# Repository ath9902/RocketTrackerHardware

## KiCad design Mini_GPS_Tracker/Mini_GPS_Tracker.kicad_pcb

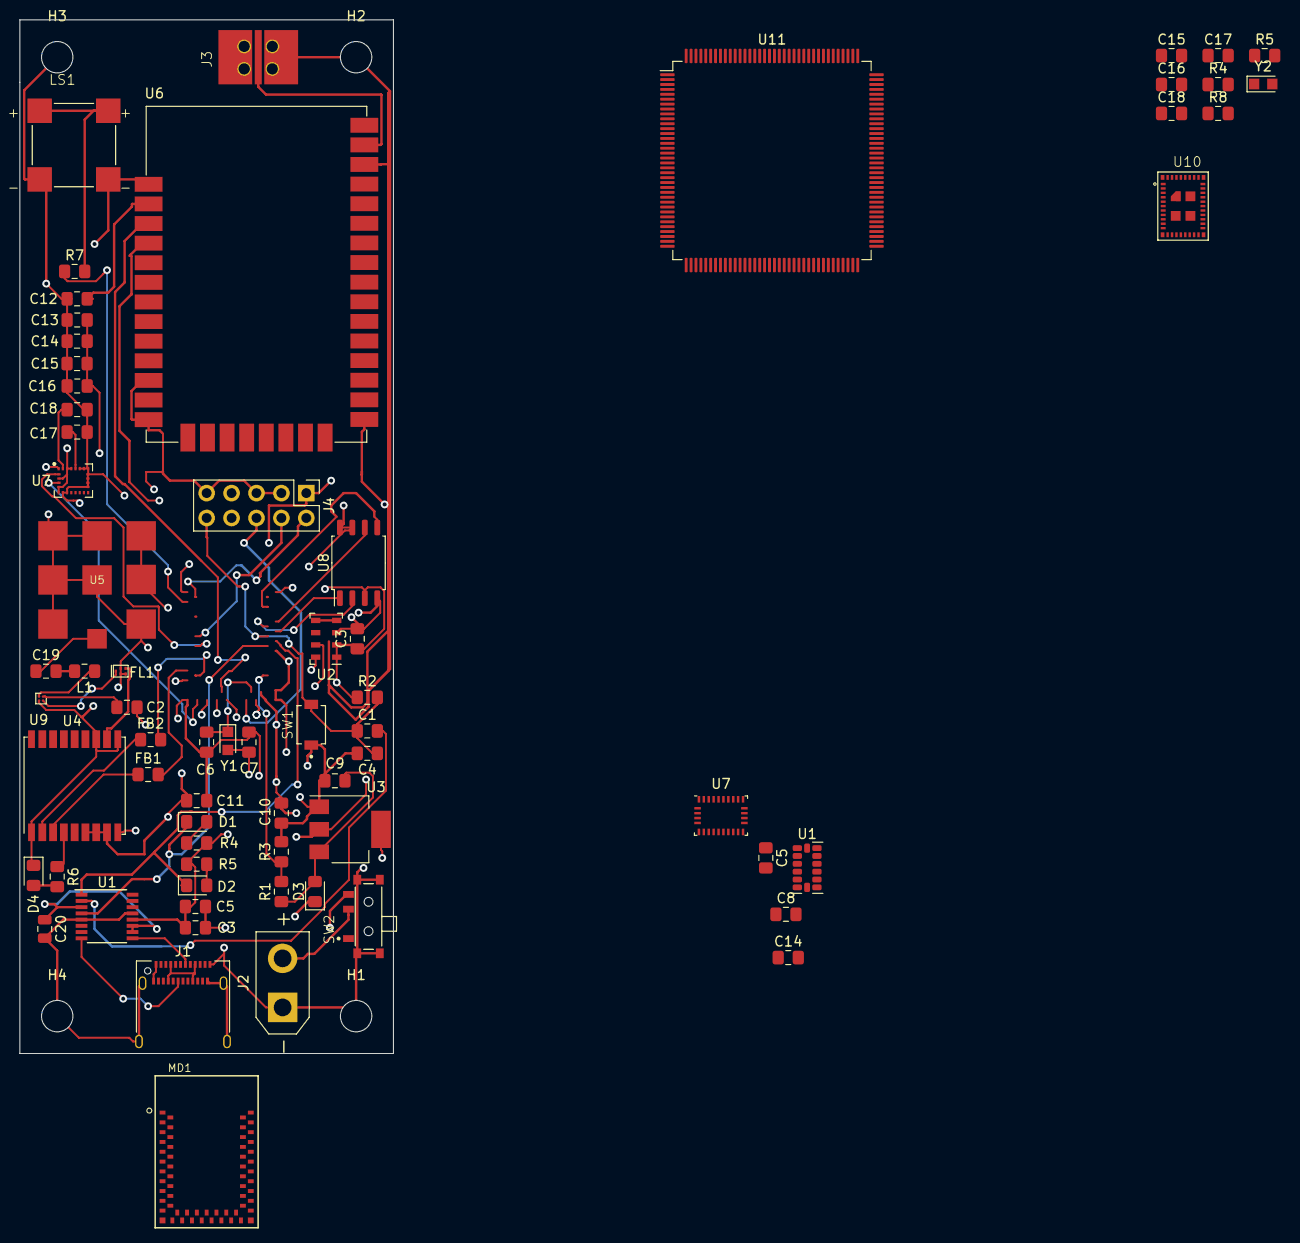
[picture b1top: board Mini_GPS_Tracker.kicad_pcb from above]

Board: 4 copper layers, 38.1 x 105.4 mm, 72 parts (0 on the bottom side), 56 nets.

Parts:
C1, C3, C5#2, C8, C11, C15, C15#2, C16, C16#2, C18: 0.1uF; C_0805_2012Metric_Pad1.15x1.40mm_HandSolder
C2: 10 pf; C_0805_2012Metric_Pad1.15x1.40mm_HandSolder
C3#2, C9: 100nF; C_0805_2012Metric_Pad1.15x1.40mm_HandSolder
C4: 1nF; C_0805_2012Metric_Pad1.15x1.40mm_HandSolder
C5, C17: 10nF; C_0805_2012Metric_Pad1.15x1.40mm_HandSolder
C6, C7: 15 pf; C_0805_2012Metric_Pad1.15x1.40mm_HandSolder
C10, C14, C14#2: 10uF; C_0805_2012Metric_Pad1.15x1.40mm_HandSolder
C12: 100pF; C_0805_2012Metric_Pad1.15x1.40mm_HandSolder
C13: 1.0uF; C_0805_2012Metric_Pad1.15x1.40mm_HandSolder
C17#2, C18#2: 22pF; C_0805_2012Metric_Pad1.15x1.40mm_HandSolder
C19: 100 nf; C_0805_2012Metric_Pad1.15x1.40mm_HandSolder
C20: 100 nf; C_0805_2012Metric
D1, D2, D4: LED; LED_0805_2012Metric_Pad1.15x1.40mm_HandSolder
D3: DIODE; D_0805_2012Metric_Pad1.15x1.40mm_HandSolder
FB1, FB2: Ferrite_Bead_Small; C_0805_2012Metric_Pad1.15x1.40mm_HandSolder
FL1: SAFFA1G58KA0F0A; Filter_1411-5_1.4x1.1mm
H1, H2, H3, H4: MountingHole_Pad; MountingHole_3.2mm_M3
J1: USB_C_Receptacle; USB_C_Receptacle_Amphenol_12401610E4-2A
J2: Screw_Terminal_01x02; AMASS_XT30UPB-F_1x02_P5.0mm_Vertical
J3: 901-10512-1; AMPHENOL_901-10512-1
J4: Conn_ARM_JTAG_SWD_10; PinHeader_2x05_P2.54mm_Vertical
L1: 6.8 nH; L_0805_2012Metric_Pad1.15x1.40mm_HandSolder
LS1: CSS-J4D20-SMT; CUI_CSS-J4D20-SMT
MD1: SPARKFUN_WRL-15376
R1, R5#2, R8: 10k; R_0805_2012Metric_Pad1.15x1.40mm_HandSolder
R2: 100K; R_0805_2012Metric_Pad1.15x1.40mm_HandSolder
R3: 3k; R_0805_2012Metric_Pad1.15x1.40mm_HandSolder
R4, R5: 1K; R_0805_2012Metric_Pad1.15x1.40mm_HandSolder
R4#2: 10K; R_0805_2012Metric_Pad1.15x1.40mm_HandSolder
R6: 750; R_0805_2012Metric_Pad1.15x1.40mm_HandSolder
R7: 0 ohm; R_0805_2012Metric_Pad1.15x1.40mm_HandSolder
SW1: SW_Push; SW_TL1015AF160QG
SW2: MLL1200S; SW_MLL1200S
U1: FT230XS; SSOP-16_3.9x4.9mm_P0.635mm
U1#2: ADXL343; LGA-14_3x5mm_P0.8mm_LayoutBorder1x6y
U2: MS5611-01BA; LGA-8_3x5mm_P1.25mm
U3: LD1117S33TR_SOT223; SOT-223-3_TabPin2
U4: MAX-8Q; ublox_MAX
U5: SGGP.12.4.A.02
U6: XBee_SMT; Digi_XBee_SMT
U7: LSM9DS1; LGA-24L_3x3.5mm_P0.43mm
U7#2: BNO055; LGA-28_5.2x3.8mm_P0.5mm
U8: W25Q128JVS; SOIC-8_5.23x5.23mm_P1.27mm
U9: MAX2686; WLP-4_0.86x0.86mm_P0.4mm
U10: LBEE5KL1DX-TEMP; XCVR_LBEE5KL1DX-TEMP
U11: STM32F413ZHTx; LQFP-144_20x20mm_P0.5mm
Y1: 32.786 KHz; Crystal_SMD_2012-2Pin_2.0x1.2mm_HandSoldering
Y2: 32.7568KHz; Crystal_SMD_2012-2Pin_2.0x1.2mm_HandSoldering

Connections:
+3V3: C2.2, C3.1, C3#2.1, C5.1, C10.1, C11.1, C13.1, C14.1, C15.1, C15#2.1, C16.1, J4.1, MD1.36, MD1.37, R2.1, R4.1, R5.1, U1.12, U2.1, U2.2, U3.2, U4.6, U4.7, U4.8, U7.1, U7.3, U7.5, U7.6, U7.22, U7.23, U7#2.3, U7#2.4, U7#2.28, U8.3, U8.7, U8.8
A1: J4.6, MD1.33
GND: C3.2, C3#2.2, C4.2, C5.2, C5#2.2, C6.2, C7.2, C8.2, C9.2, C10.2, C11.2, C12.2, C13.2, C14.2, C14#2.2, C15.2, C15#2.2, C16.2, C16#2.2, C17.2, C17#2.2, C18.2, C18#2.1, C20.2, D4.1, FL1.2, FL1.3, FL1.5, H1.1, H2.1, H3.1, H4.1, J1.A1, J1.A12, J1.B1, J1.B12, J1.S1, J2.1, J3.G1, J3.G2, J3.G11, J3.G12, J3.G21, J3.G22, J4.3, J4.5, J4.9, LS1.M1, LS1.M2, MD1.1, MD1.22, MD1.38, MD1.39, MD1.47, MD1.59, R3.2, R4#2.2, R5#2.2, R8.1, SW1.1, SW2.G1, SW2.G2, SW2.G3, SW2.G4, U1.5, U1.13, U1#2.2, U1#2.4, U1#2.5, U2.3, U3.1, U4.1, U4.10, U4.12, U5.GND1, U5.GND2, U5.GND3, U5.GND4, U5.GND5, U5.GND6, U5.GND7, U5.GND9, U6.1, U6.11, U6.13, U6.22, U6.35, U7.7, U7.8, U7.14, U7.15, U7.16, U7.17, U7.18, U7.19, U7.20, U7#2.2, U7#2.10, U7#2.15, U7#2.16, U7#2.18, U7#2.25, U8.4, U9.B2, U10.1, U10.12, U10.19, U10.21, U10.29, U10.35, U10.40, U10.42, U10.43, U10.44, U10.45, U10.46
GPS_RX: FB1.2, MD1.17
GPS_TX: FB2.2, MD1.18
unnamed: C2.1, U9.A1
unnamed: C5#2.1, U1#2.1
unnamed: C6.1, MD1.34, Y1.1
unnamed: C7.1, MD1.35, Y1.2
unnamed: C9.1, D3.2, R1.1, U3.3
unnamed: C12.1, U6.2
unnamed: C8.1, C14#2.1, U1#2.6
unnamed: C16#2.1, U7#2.9
unnamed: C17.1, C17#2.1, U7.21, U7#2.26, Y2.1
unnamed: C18.1, U7.24
unnamed: C18#2.2, U7#2.27, Y2.2
unnamed: C19.1, U5.RF
unnamed: C19.2, L1.2
unnamed: C20.1, U1.3, U1.10, U1.11
unnamed: D1.2, R4.2
unnamed: D2.2, R5.2
unnamed: D3.1, SW2.3
unnamed: D4.2, R6.2
unnamed: FB1.1, U4.3
unnamed: FB2.1, U4.2
unnamed: FL1.1, U9.A2
unnamed: FL1.4, U4.11
unnamed: J1.A4, J1.A9, J1.B4, J1.B9
unnamed: J1.A7, U1.9
unnamed: J1.B7, U1.8
unnamed: J2.2, SW2.2
unnamed: J3.1, U6.36
unnamed: L1.1, U9.B1
unnamed: LS1.P1, LS1.P2, R7.2
unnamed: R4#2.1, U7#2.17
unnamed: R5#2.1, U7#2.6
unnamed: R6.1, U4.4
unnamed: R8.2, U7#2.5
unnamed: U2.4, U2.5
unnamed: U7.12, U7#2.12
unnamed: U7.13, U7#2.13
unnamed: U10.32, U10.33
Pressure_SCL: MD1.19, U2.8
Pressure_SDA: MD1.25, U2.7
RESET: C1.1, C4.1, J4.10, MD1.50, R2.2, SW1.2
RTS: C1.2, U1.2
RXI: D1.1, MD1.48, U1.4
SWDCK: J4.4, MD1.10
SWDIO: J4.2, MD1.2
TRANS_RX: MD1.27, U6.4
TRANS_TX: MD1.28, U6.3
TX0: D2.1, MD1.49, U1.1
buzzer: MD1.3, R7.1
cs_flash: MD1.51, U8.1
gps_reset: MD1.29, U4.9
v_measure: MD1.42, R1.2, R3.1

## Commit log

2020-03-15 project started
2020-03-15 added circuits
2020-03-17 added pyro
2020-03-17 added example pyro
2020-03-18 added datasheets and worked on artemis module"
2020-03-18 added hichary labels
2020-03-18 added usb
2020-03-18 updated labels;
2020-03-18 added documentation
2020-03-19 started 9dof
2020-03-21 create mini gps tracker
2020-03-21 updates to routing
2020-03-21 worked on routing
2020-03-21 updated antenna;
2020-03-21 added 9dof
2020-03-24 schamatics finalized
2020-03-27 added routing
2020-03-28 updated routing
2020-03-29 trying to do a 4 layer pcb
2020-03-29 all artemis connections routed
2020-03-29 all tracks routed
2020-03-29 Add files via upload
    Added Apollo data sheet
2020-03-29 fixed tx route
2020-03-29 Add files via upload
    Mapping of Arteumus pins and associated function to schematic pin assignemnts
2020-03-30 added power and power pours
2020-03-31 Add files via upload
    Changed U1
    Changed footprint of JTAG and moved lots of stuff up
2020-03-31 Add files via upload
    Ground pour
2020-03-31 updates to routing and fix commit
2020-03-31 update sensors
2020-03-31 added 200g accel
2020-03-31 updated usb"
2020-04-03 added stm chip
2020-04-04 added bluetooth wifi module
2020-04-04 Adding BNO055 Motion co-processor
2020-04-04 Adding BNO055 motion co-processor
2020-04-04 added motion
2020-04-09 added stm core connections
2020-04-09 moved parts
2020-04-18 updated core
2020-04-18 added back usb driver chip
2020-04-18 added back usb circuit
2020-04-20 Add files via upload
    Updates schematics
2020-04-20 Add files via upload
    Chip MCU docs
2020-04-21 Add files via upload
    STM32F413VGT6 Chip data sheet
2020-04-21 Add files via upload
    Adding 100 pin MCU
2020-04-21 Add files via upload
    Adding other sheets
2020-04-21 Add files via upload
    100 Pin MCH changes
2020-04-21 Add files via upload
    STM32F413xG/H Chip changes
2020-04-27 Add files via upload
    Making update for 100 pin CPU
2020-05-09 Add files via upload
    Splitting board into modules
2020-05-09 Add files via upload
    Breaking out more pins
2020-05-10 Add files via upload
    More changes - USB, WiFi/BT, Buzzer, Siren-LED Flasher
2020-05-13 Add files via upload
    Added RFM95 board
